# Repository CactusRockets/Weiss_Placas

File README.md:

# Placa de Iluminação Weiss

Placa de acionamento de iluminação desenvolvida em **KiCad**, responsável por controlar dois LEDs com o objetivo de iluminar a parte interna do weiss através de uma chave (push-button), a partir de uma alimentação externa de **3.3V**. O projeto foi desenhado para ser simples e robusto, priorizando facilidade de montagem (todos os componentes em THT) e baixo custo.

## Visão geral do circuito

O circuito é alimentado externamente via um conector **JST XH de 2 vias**, que entrega +3.3V e GND à placa. Essa alimentação passa por um **push-button (SW1)**, que atua como chave liga/desliga geral do circuito. A partir do botão, a alimentação se divide em **dois ramos em paralelo**, cada um composto por um resistor limitador de corrente em série com um LED de alta potência:

Ou seja: quando o botão é pressionado (ou travado, dependendo do tipo de chave utilizada), o circuito fecha e os dois LEDs acendem simultaneamente. Cada LED possui seu próprio resistor, de forma que o brilho e a corrente de cada um são definidos de forma independente — isso evita que uma eventual diferença entre os dois LEDs (tensão direta, tolerância) afete o outro ramo, como aconteceria se estivessem em paralelo direto sob um único resistor.

Foram incluídas **PWR_FLAGs** no esquemático em +3.3V e GND. Elas não fazem parte do circuito fisicamente: servem apenas para informar ao ERC (Electrical Rules Checker) do KiCad que esses nós de alimentação são supridos por uma fonte externa (o JST), evitando falsos positivos de "net não alimentada".

## Componentes

| Referência | Componente | Footprint / Símbolo | Função |
|---|---|---|---|
| **JST1** | Conector JST XH 2 vias | `Connector_JST:JST_XH_B2B-XH-A_1x02_P2.50mm_Vertical` | Entrada de alimentação externa (+3.3V e GND) |
| **SW1** | Push-button | `Button_Switch_SMD:SW_SPST_B3S-1000` (footprint na placa: `SW_SPST_Omron_B3F-40xx-CRD`) | Chave de acionamento (liga/desliga) do circuito |
| **R1** | Resistor 15Ω | `Resistor_THT:R_Axial_DIN0204_L3.6mm_D1.6mm_P7.62mm_Horizontal` | Limitador de corrente do LED U1 |
| **R2** | Resistor 15Ω | `Resistor_THT:R_Axial_DIN0204_L3.6mm_D1.6mm_P7.62mm_Horizontal` | Limitador de corrente do LED U2 |
| **U1** | LED de alta potência | `LED_THT:LED_D5.0mm` | Iluminação (ramo 1) |
| **U2** | LED de alta potência | `LED_THT:LED_D5.0mm` | Iluminação (ramo 2) |

> Os símbolos `JST_basic`, `Push_button_4_pin` e `Led_High` são customizados e estão definidos na biblioteca local `CRD_KICAD.kicad_sym`, criada para padronizar os componentes usados nos projetos da Cactus Rockets.

## Funcionamento

O funcionamento da placa é puramente analógico/passivo — não há microcontrolador ou lógica embarcada:

1. A alimentação de +3.3V chega pelo conector **JST1**.
2. O **SW1** atua como interruptor: enquanto estiver fechado, a corrente flui para os dois ramos de LED.
3. Cada ramo (R + LED) limita a corrente que passa pelo respectivo LED, garantindo que ele opere dentro da faixa segura especificada pelo fabricante, evitando queima por excesso de corrente.
4. O retorno de ambos os ramos é feito para o **GND** comum da placa, que fecha o circuito de volta à fonte externa.

Por não haver controle ativo (PWM, microcontrolador, etc.), o brilho dos LEDs é fixo e definido unicamente pelo valor dos resistores e pela tensão de alimentação — não há dimerização nem controle remoto nesta versão da placa.

## Cálculo dos resistores limitadores

O valor do resistor limitador é definido pela equação pela lei de ohm:

```
R = (V_fonte - V_LED) / I_LED
```

Com `V_fonte = 3.3V` e `R = 15Ω`, a corrente em cada ramo depende da tensão direta (V_f) do LED utilizado. Por exemplo:

- Para um LED com V_f ≈ 2.0V → I ≈ (3.3 − 2.0) / 15 ≈ **87 mA**
- Para um LED com V_f ≈ 3.0V → I ≈ (3.3 − 3.0) / 15 ≈ **20 mA**

## Placa (PCB)

- Placa de **1.6mm** de espessura (FR4 padrão), com contorno definido em `Edge.Cuts`.
- Todos os componentes são **THT** (through-hole), facilitando a montagem manual e a soldagem.
- Footprints utilizados:
  - `CRD_Footprints:SW_SPST_Omron_B3F-40xx-CRD` (SW1)
  - `LED_THT:LED_D5.0mm` / `CRD_Footprints:LED_D5.0mm-CRD` (U1, U2)
  - `Resistor_THT:R_Axial_DIN0204_L3.6mm_D1.6mm_P7.62mm_Horizontal` (R1, R2)
  - `Connector_JST:JST_XH_B2B-XH-A_1x02_P2.50mm_Vertical` (JST1)

## Arquivos do projeto

| Arquivo | Descrição |
|---|---|
| `Placa_de_Iluminação_Weiss.kicad_sch` | Esquemático elétrico da placa |
| `Placa_de_Iluminação_Weiss.kicad_pcb` | Layout da placa (PCB) |
| `Placa_de_Iluminação_Weiss.kicad_pro` | Arquivo de projeto do KiCad |
| `CRD_KICAD.kicad_sym` | Biblioteca de símbolos customizados da Cactus Rockets |
| `fp-lib-table` | Tabela de bibliotecas de footprints usadas no projeto |

# Placa de Processamento — Weiss

Placa eletrônica central do projeto **Weiss**, desenvolvida em **KiCad**, responsável por concentrar o processamento, a aquisição de dados, o armazenamento local e as interfaces de telemetria e sinalização do sistema.

O projeto utiliza um **ESP32 DevKit V1** como controlador principal e integra módulos de rádio LoRa, GPS, cartão microSD, barômetro, unidade inercial, buzzer, LED de status e conectores para sinais externos.

> **Atenção:** esta documentação foi levantada a partir do esquemático e do layout da placa. Antes da fabricação ou da integração ao veículo, execute ERC/DRC no KiCad e confira a pinagem com o firmware e com os módulos físicos utilizados.

## Visão geral

Principais recursos:

- ESP32 DevKit V1 como unidade de processamento;
- telemetria por módulo LoRa **E22-400T30D**;
- posicionamento por módulo GPS serial;
- registro de dados em cartão microSD via SPI;
- medição de pressão e altitude com **BMP390** via I²C;
- medição inercial com **MPU6050** via I²C;
- buzzer e LED para sinalização local;
- duas entradas provenientes de optoacopladores externos;
- duas linhas de interface identificadas como `SKIB1` e `SKIB2`;
- alimentação por bateria de 9 V, com chave e duas linhas reguladas de 5 V;
- conectores JST de 2 vias para alimentação e sinais auxiliares.

## Arquitetura elétrica

```mermaid
flowchart LR
    B["Bateria 9 V"] --> S["Chave SS-5GL"]
    S --> VIN["VIN"]
    VIN --> R1["Regulador 5 V — VOUT"]
    VIN --> R2["Regulador 5 V — VOUT_LORA"]
    R1 --> ESP["ESP32 DevKit V1"]
    R2 --> LORA["LoRa E22-400T30D"]
    ESP --> V33["Barramento 3,3 V"]
    V33 --> GPS["GPS"]
    V33 --> I2C["BMP390 + MPU6050"]
    V33 --> SD["microSD"]
    ESP <--> LORA
    ESP <--> GPS
    ESP <--> I2C
    ESP <--> SD
```

A chave `U$12` conecta o terminal comum `VIN` ao contato associado a `V_BATTERY`; o outro contato da chave aparece sem conexão no esquemático. A partir de `VIN`, dois reguladores independentes, ambos identificados como **5 V**, geram:

- `VOUT`: alimentação do pino `VIN` do ESP32 DevKit V1;
- `VOUT_LORA`: alimentação dedicada do módulo LoRa.

O barramento de **3,3 V** é distribuído a partir do pino `3V3` do ESP32 para os sensores, GPS, microSD e conectores auxiliares. Todos os subsistemas da placa compartilham o mesmo GND.

## Mapeamento de pinos do ESP32

| GPIO | Rede | Interface / função |
|---:|---|---|
| 2 | `LED1` | LED de status |
| 4 | `TX1` | TX do ESP32 para RX do GPS |
| 5 | `CS` | Chip Select do microSD |
| 12 | `SKIB2` | Linha externa SKIB2 |
| 13 | `SKIB1` | Linha externa SKIB1 |
| 14 | `BUZZER` | Acionamento do buzzer |
| 15 | `RX1` | RX do ESP32 vindo do TX do GPS |
| 16 | `RX2` | RX do ESP32 vindo do TXD do LoRa |
| 17 | `TX2` | TX do ESP32 para RXD do LoRa |
| 18 | `CLK` | Clock SPI do microSD |
| 19 | `MISO` | Dados SPI do microSD para o ESP32 |
| 21 | `SDA` | Dados do barramento I²C |
| 22 | `SCL` | Clock do barramento I²C |
| 23 | `MOSI` | Dados SPI do ESP32 para o microSD |
| 32 | `M1` | Seleção de modo do LoRa |
| 33 | `M0` | Seleção de modo do LoRa |
| 34 | `OPTOACOPLADOR2` | Entrada externa isolada |
| 35 | `OPTOACOPLADOR1` | Entrada externa isolada |

> Os GPIOs 34 e 35 do ESP32 são somente de entrada. As linhas `SKIB1` e `SKIB2` chegam diretamente ao ESP32 no esquema apresentado; elas são sinais lógicos e **não devem acionar cargas pirotécnicas diretamente**. Qualquer carga desse tipo exige estágio externo de potência, intertravamentos e isolamento apropriados.

## Interfaces dos módulos

### LoRa E22-400T30D

| Pino do módulo | Rede da placa | Destino |
|---|---|---|
| `VCC` | `VOUT_LORA` | Alimentação dedicada de 5 V |
| `GND` | `GND` | Referência comum |
| `TXD` | `RX2` | GPIO16 do ESP32 |
| `RXD` | `TX2` | GPIO17 do ESP32 |
| `M0` | `M0` | GPIO33 do ESP32 |
| `M1` | `M1` | GPIO32 do ESP32 |
| `AUX` | Sem conexão | Reservado no layout atual |

### GPS

| Pino do módulo | Rede da placa | Destino |
|---|---|---|
| `VCC` | `3V3` | Alimentação de 3,3 V |
| `GND` | `GND` | Referência comum |
| `RX` | `TX1` | GPIO4 do ESP32 |
| `TX` | `RX1` | GPIO15 do ESP32 |

### BMP390 e MPU6050

Os dois sensores compartilham o barramento I²C:

| Sinal | GPIO do ESP32 | Módulos |
|---|---:|---|
| `SDA` | 21 | BMP390 e MPU6050 |
| `SCL` | 22 | BMP390 e MPU6050 |
| `3V3` | — | Alimentação |
| `GND` | — | Referência comum |

No layout atual, os pinos auxiliares `CS`, `SDO` e `INT` do BMP390 e `XDA`, `XCL`, `ADO` e `INT` do MPU6050 não são utilizados.

### Cartão microSD

| Sinal | GPIO do ESP32 |
|---|---:|
| `CS` | 5 |
| `CLK` | 18 |
| `MISO` | 19 |
| `MOSI` | 23 |
| `VCC` | 3,3 V |
| `GND` | GND |

## Conectores auxiliares

| Referência | Identificação | Pino 1 | Pino 2 |
|---|---|---|---|
| `U$10` | Bateria 9 V | `V_BATTERY` | `GND` |
| `U$6` | Skibs | `SKIB1` | `SKIB2` |
| `U$7` | Optoacopladores | `OPTOACOPLADOR1` | `OPTOACOPLADOR2` |
| `U$4` | Buzzer / 3,3 V | `BUZZER` | `3V3` |
| `U$5` | GND / 3,3 V | `3V3` | `GND` |

## Componentes principais

| Referência | Componente | Função |
|---|---|---|
| `U$11` | ESP32 DevKit V1 | Processamento e controle das interfaces |
| `U$2` | E22-400T30D | Comunicação LoRa |
| `U$3` | GPS Module | Posicionamento e referência de tempo |
| `U$1` | BMP390 | Pressão atmosférica e altitude |
| `U$9` | MPU6050 | Acelerômetro e giroscópio |
| `U$8` | MicroSD Small Reader | Armazenamento local de dados |
| `IC1` | Regulador 5 V | Alimentação `VOUT` do ESP32 |
| `IC2` | Regulador 5 V | Alimentação `VOUT_LORA` |
| `U$12` | Chave SS-5GL | Comutação da alimentação de entrada |
| `SP1` | AL60P | Buzzer |
| `LED1` | LED vermelho 5 mm | Indicação visual |
| `R1` | 220 Ω | Limitação de corrente do LED |
| `R2` | 46 Ω | Componente auxiliar; o pad 2 está sem conexão funcional no layout atual |
| `U$4` a `U$7`, `U$10` | JST 2,54 mm, 2 vias | Alimentação e sinais externos |

## Dimensões e construção da PCB

- dimensões aproximadas do contorno: **150 × 80 mm**;
- espessura configurada: **1,6 mm**;
- placa de duas camadas de cobre (`F.Cu` e `B.Cu`);
- componentes predominantemente THT e módulos montados por barras de pinos;
- planos de cobre e trilhas de alimentação de maior largura;
- footprints personalizados disponíveis na biblioteca local `Weiss.pretty`.

## Arquivos do projeto

| Caminho | Descrição |
|---|---|
| `Esquema.kicad_pro` | Projeto principal do KiCad |
| `Esquema.kicad_sch` | Esquemático elétrico |
| `Esquema.kicad_pcb` | Layout da PCB |
| `Esquema.svg` | Exportação vetorial do esquemático |
| `Esquema.kicad_dru` | Regras personalizadas da placa |
| `Weiss.pretty/` | Biblioteca local de footprints |
| `BibliotecasCRD-KiCad-main/` | Bibliotecas auxiliares utilizadas pelo projeto |
| `fp-lib-table` | Tabela de bibliotecas de footprints |
| `sym-lib-table` | Tabela de bibliotecas de símbolos |

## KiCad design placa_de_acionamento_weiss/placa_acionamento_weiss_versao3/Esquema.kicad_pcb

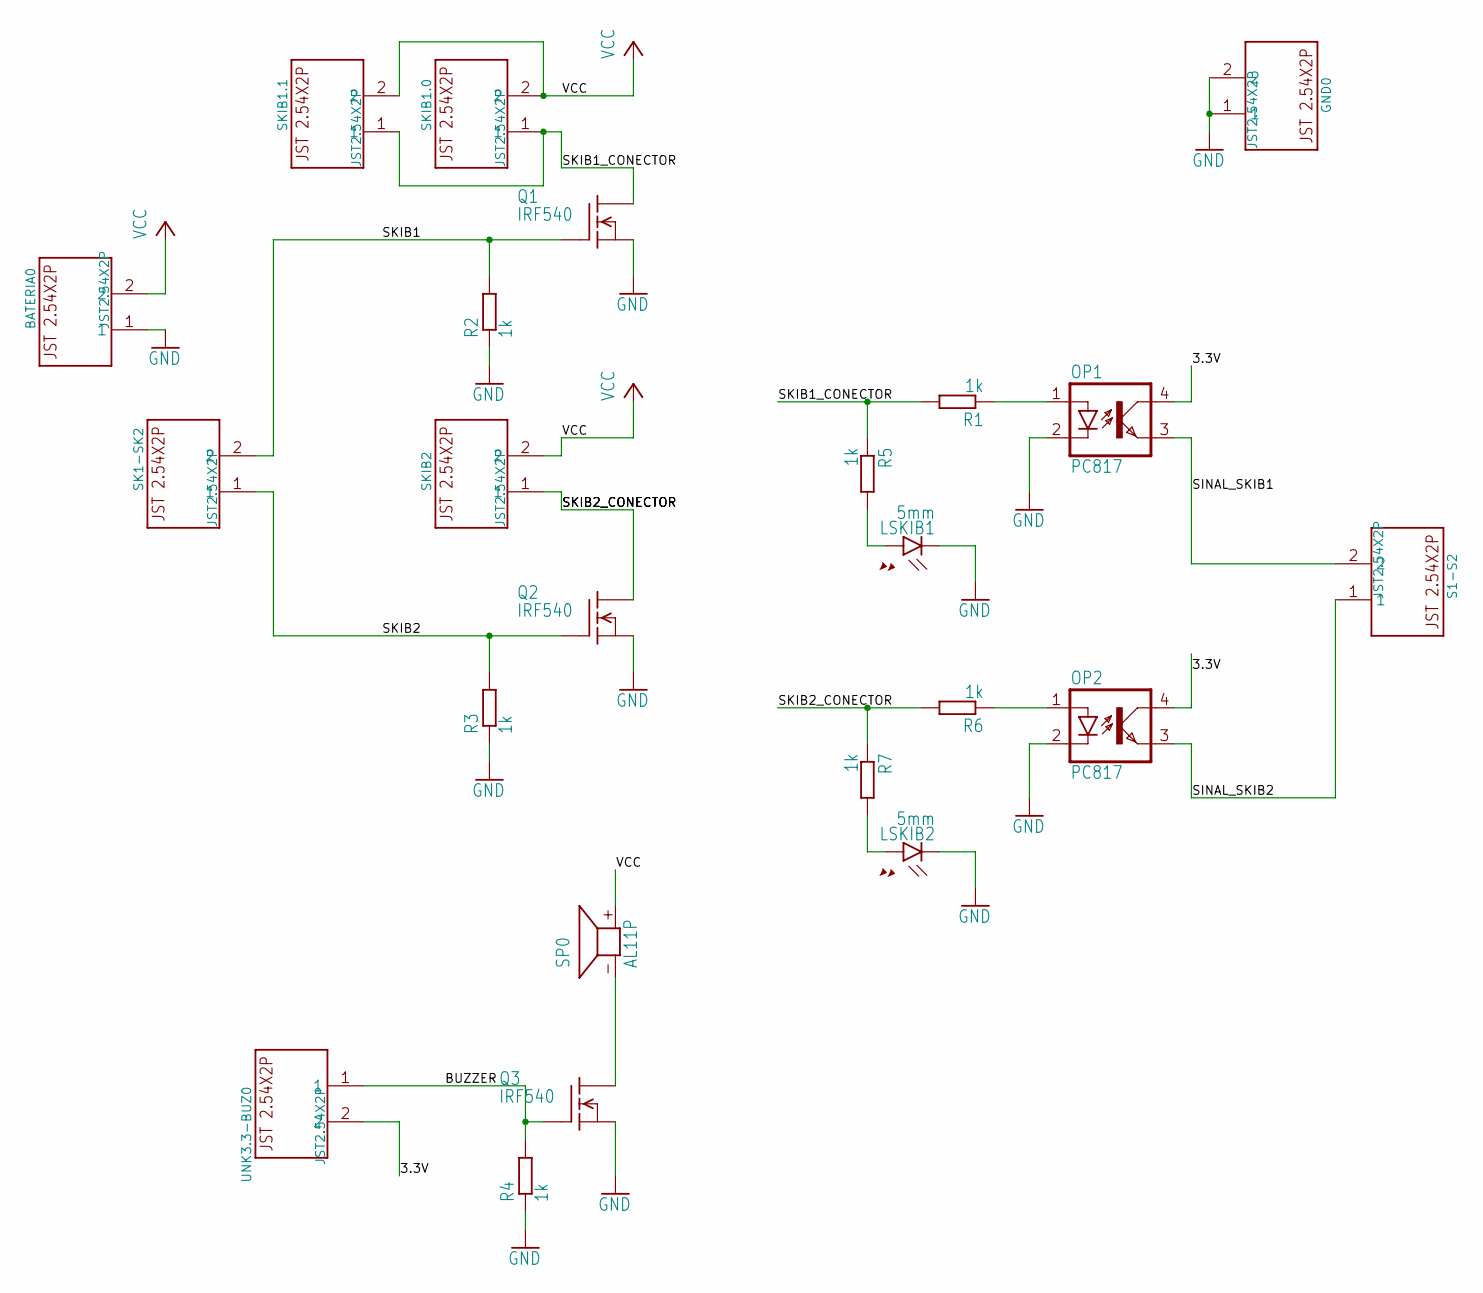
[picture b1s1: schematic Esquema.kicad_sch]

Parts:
BATERIA0: JST2.54X2P; JST2.54X2P_FOOTPRINT
GND0: JST2.54X2P; JST2.54X2P_FOOTPRINT
LSKIB1, LSKIB2: 5mm; LED5MM
OP1, OP2: PC817; DIL04
Q1, Q2, Q3: IRF540; TO220
R1, R2, R3, R4, R5, R6, R7: 1k; 0207_10
S1-S2: JST2.54X2P; JST2.54X2P_FOOTPRINT
SK1-SK2: JST2.54X2P; JST2.54X2P_FOOTPRINT
SKIB1.0, SKIB1.1, SKIB2: JST2.54X2P; JST2.54X2P_FOOTPRINT
SP0: AL11P
UNK3.3-BUZ0: JST2.54X2P; JST2.54X2P_FOOTPRINT

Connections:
3.3V: OP1.4 (COL), OP2.4 (COL), UNK3.3-BUZ0.2
BUZZER: Q3.1 (G), R4.2, UNK3.3-BUZ0.1
GND: BATERIA0.1, GND0.1, GND0.2, LSKIB1.K (C), LSKIB2.K (C), OP1.2 (C), OP2.2 (C), Q1.3 (S), Q2.3 (S), Q3.3 (S), R2.1, R3.1, R4.1
unnamed: LSKIB2.A, R7.2
unnamed: Q3.2 (D), SP0.- (1)
unnamed: LSKIB1.A, R5.2
unnamed: OP1.1 (A), R1.1
unnamed: OP2.1 (A), R6.1
SINAL_SKIB1: OP1.3 (EMIT), S1-S2.2
SINAL_SKIB2: OP2.3 (EMIT), S1-S2.1
SKIB1: Q1.1 (G), R2.2, SK1-SK2.2
SKIB1_CONECTOR: Q1.2 (D), R1.2, R5.1, SKIB1.0.1, SKIB1.1.1
SKIB2: Q2.1 (G), R3.2, SK1-SK2.1
SKIB2_CONECTOR: Q2.2 (D), R6.2, R7.1, SKIB2.1
VCC: BATERIA0.2, SKIB1.0.2, SKIB1.1.2, SKIB2.2, SP0.+ (2)

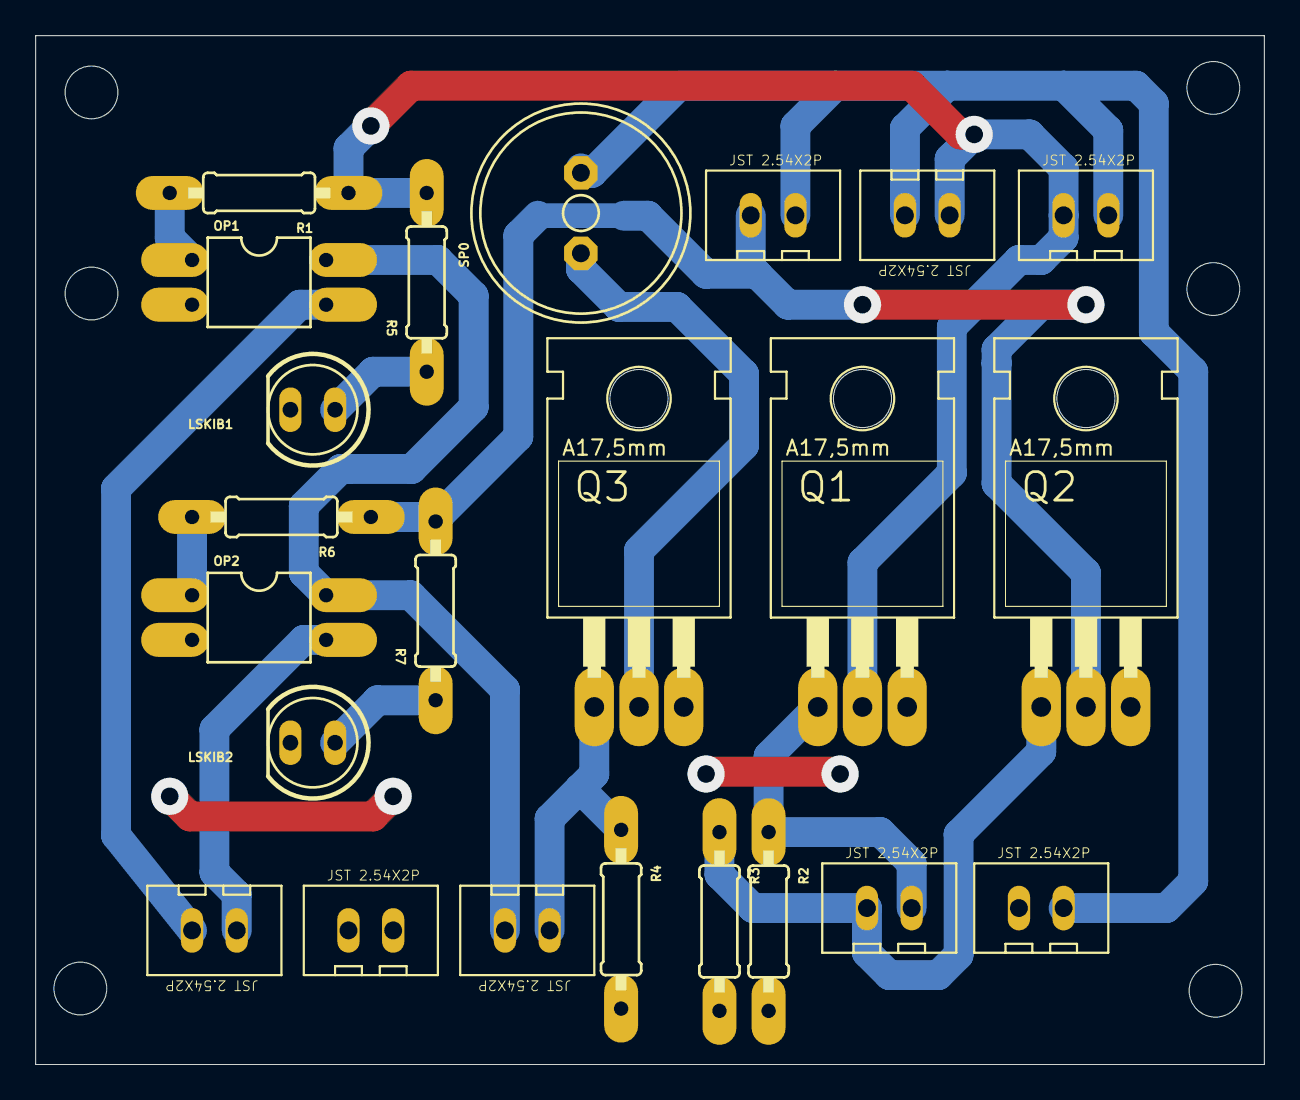
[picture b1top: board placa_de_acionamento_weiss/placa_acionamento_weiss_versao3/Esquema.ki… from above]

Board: 2 copper layers, 69.8 x 58.5 mm, 29 parts (0 on the bottom side), 15 nets.

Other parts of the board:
UNK_HOLE_0: dummyfp0
UNK_HOLE_1: dummyfp1
UNK_HOLE_2: dummyfp2
UNK_HOLE_3: dummyfp3
UNK_HOLE_4: dummyfp4
UNK_HOLE_5: dummyfp5

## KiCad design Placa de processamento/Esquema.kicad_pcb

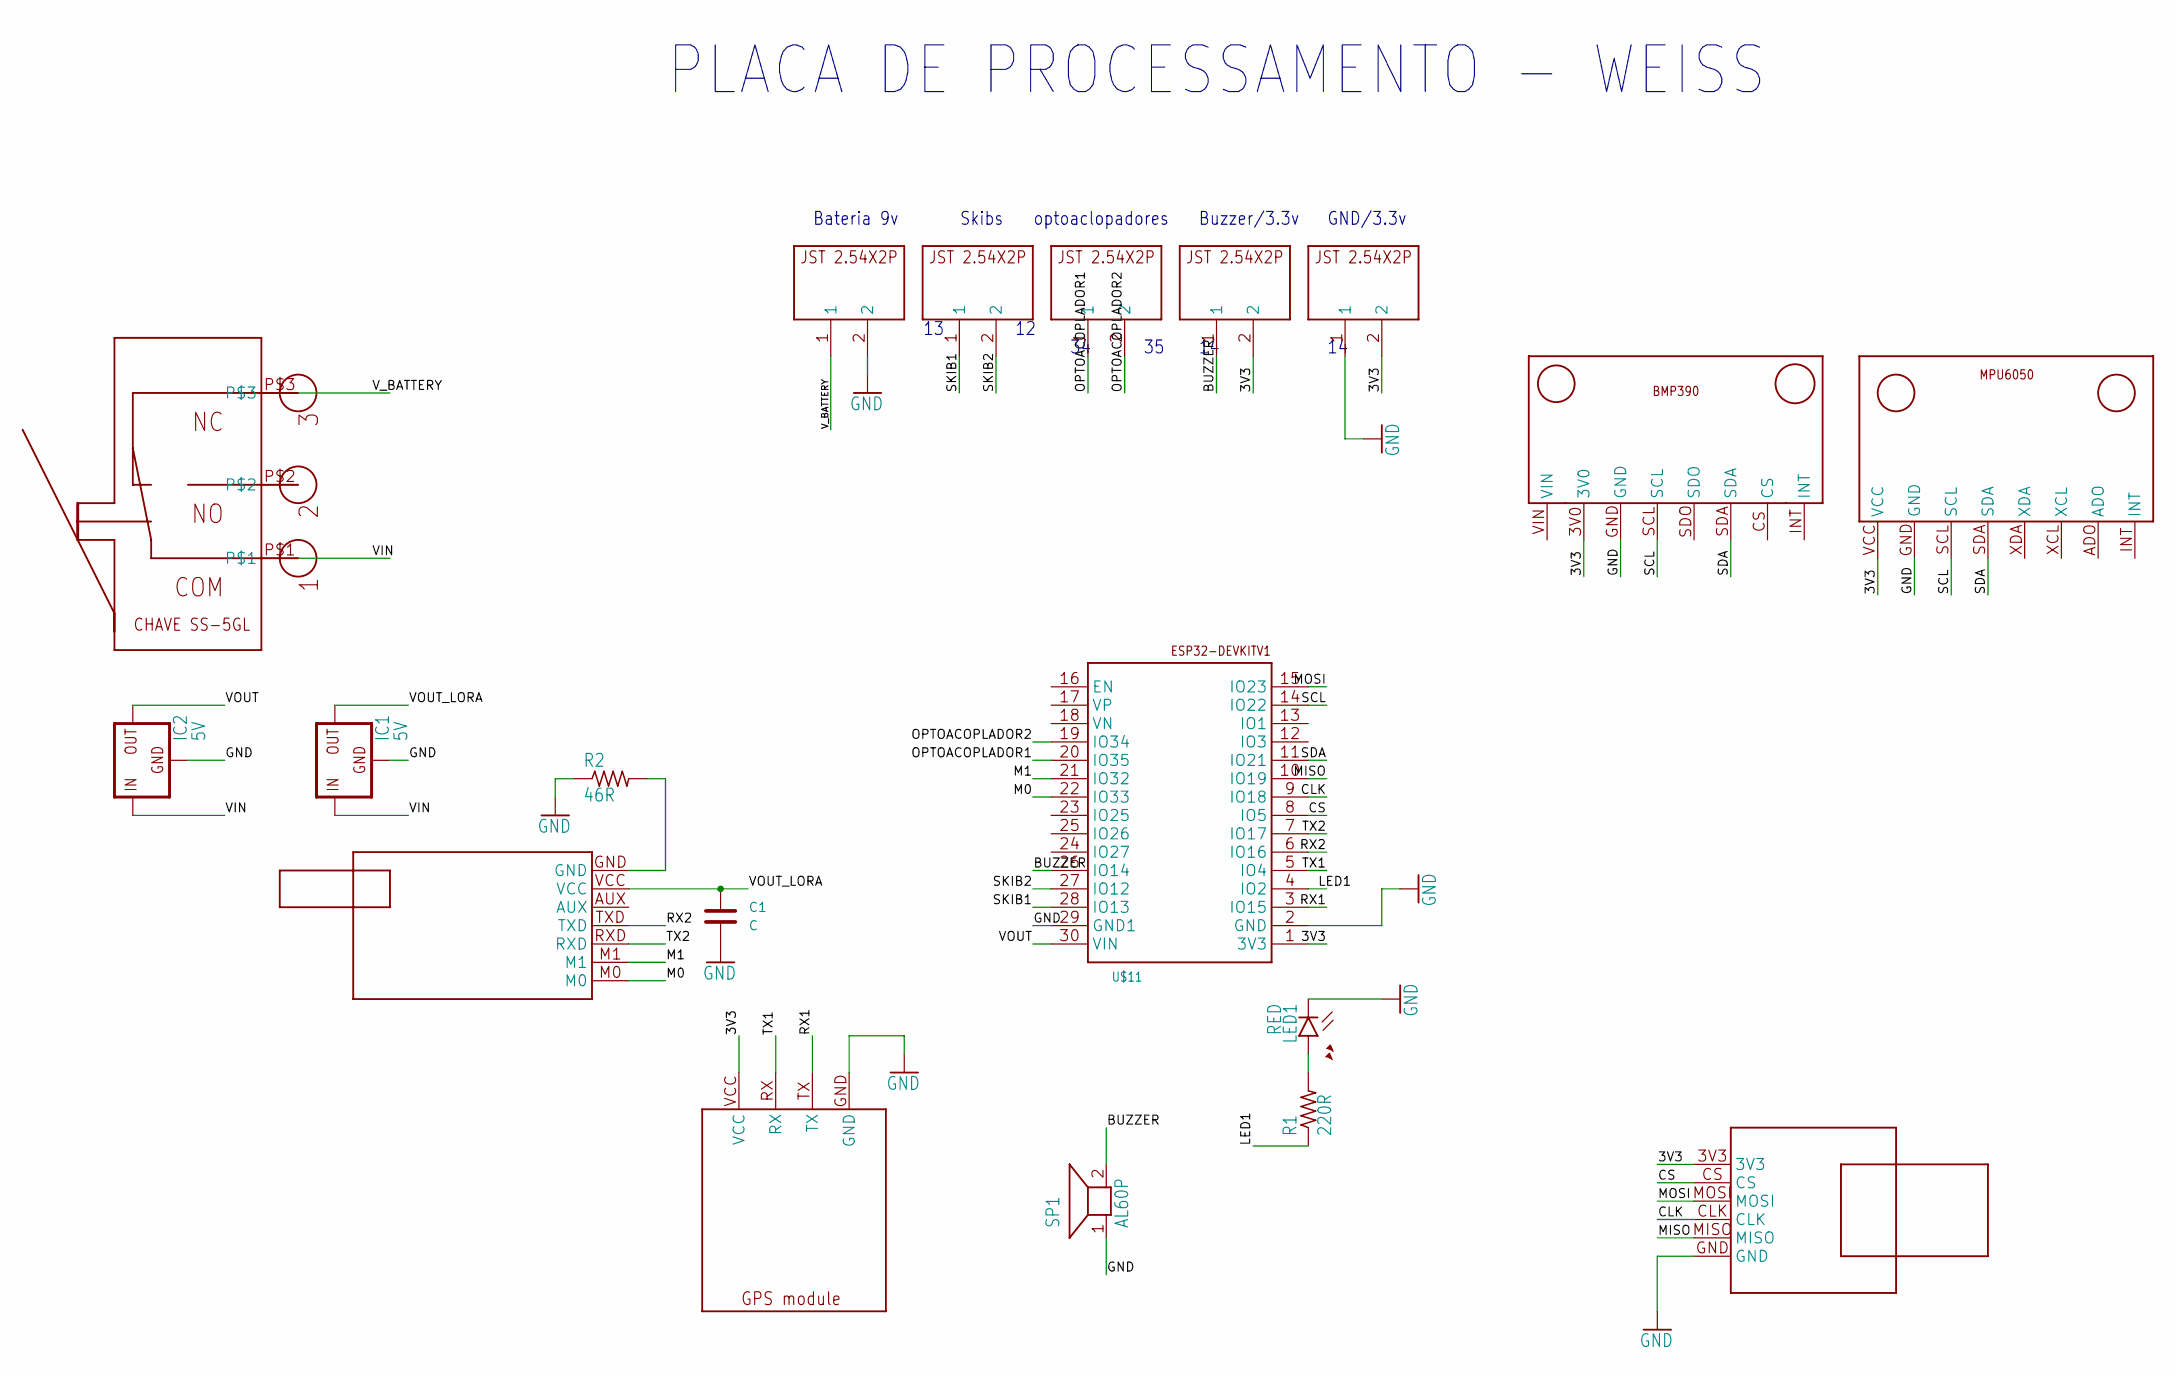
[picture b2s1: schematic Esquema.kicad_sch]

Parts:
C1: C
IC1, IC2: 5V; 78XXL
LED1: RED; LED5MM
R1: 220R; 0309_12
R2: 46R; 0309_12
SP1: AL60P
U$1: BMP390V1; BMP390_FOOTPRINT
U$2: E22-400T30D; E22-400T30D_FOOTPRINT
U$3: GPS_MODULE; GPS_MODULE_FOOTPRINT
U$4, U$5, U$6, U$7: JST2.54X2P; JST2.54X2P_FOOTPRINT
U$8: MICROSD_SMALL_READER; MICROSD_SMALL_READER_FOOTPRINT
U$9: MPU6050V1; MPU6050_FOOTPRINT
U$10: JST2.54X2P; JST2.54X2P_FOOTPRINT_39051337
U$11: ESP32DEVKITV1; ESP32-DEVKITV1
U$12: CHAVE_SS-5GL; CHAVESS-5GL

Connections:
/3V3: U$1.3V0, U$3.VCC, U$4.2, U$8.3V3, U$9.VCC, U$10.2, U$11.1 (3V3)
/BUZZER: SP1.2, U$4.1, U$11.26 (IO14)
/CLK: U$8.CLK, U$11.9 (IO18)
/CS: U$8.CS, U$11.8 (IO5)
/LED1: R1.1, U$11.4 (IO2)
/M0: U$2.M0, U$11.22 (IO33)
/M1: U$2.M1, U$11.21 (IO32)
/MISO: U$8.MISO, U$11.10 (IO19)
/MOSI: U$8.MOSI, U$11.15 (IO23)
/OPTOACOPLADOR1: U$5.1, U$11.20 (IO35)
/OPTOACOPLADOR2: U$5.2, U$11.19 (IO34)
/RX1: U$3.TX, U$11.3 (IO15)
/RX2: U$2.TXD, U$11.6 (IO16)
/SCL: U$1.SCL, U$9.SCL, U$11.14 (IO22)
/SDA: U$1.SDA, U$9.SDA, U$11.11 (IO21)
/SKIB1: U$6.1, U$11.28 (IO13)
/SKIB2: U$6.2, U$11.27 (IO12)
/TX1: U$3.RX, U$11.5 (IO4)
/TX2: U$2.RXD, U$11.7 (IO17)
/VIN: IC1.IN, IC2.IN, U$12.P$1
/VOUT: IC2.OUT, U$11.30 (VIN)
/VOUT_LORA: C1.1, IC1.OUT, U$2.VCC
/V_BATTERY: U$7.1, U$12.P$3
GND: C1.2, IC1.GND, IC2.GND, LED1.K (C), R2.1, SP1.1, U$1.GND, U$3.GND, U$7.2, U$8.GND, U$9.GND, U$10.1, U$11.2 (GND), U$11.29 (GND1)
unnamed: LED1.A, R1.2
unnamed: R2.2, U$2.GND

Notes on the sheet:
Bateria 9v
PLACA DE PROCESSAMENTO - WEISS
Skibs
GND/3.3v
Buzzer/3.3v
optoaclopadores

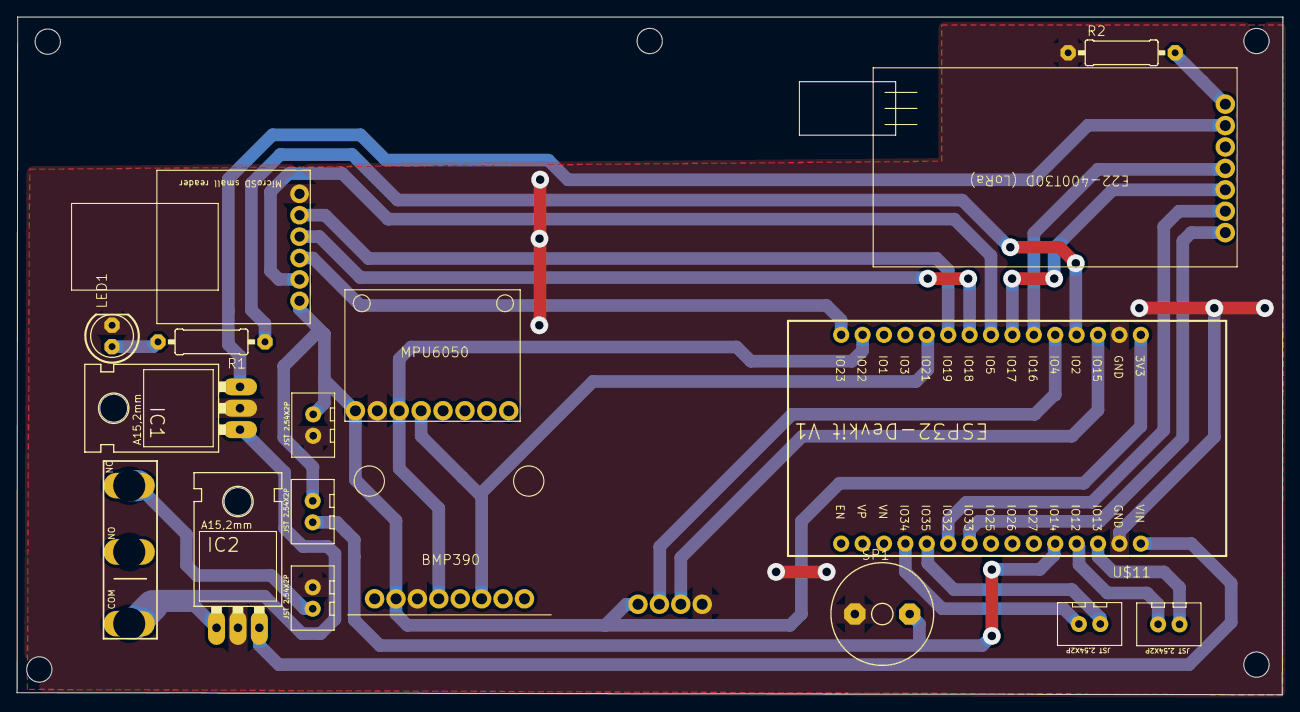
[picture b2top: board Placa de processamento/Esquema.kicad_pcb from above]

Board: 2 copper layers, 150.2 x 80.4 mm, 23 parts (1 on the bottom side), 26 nets.

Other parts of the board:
UNK_HOLE_0: dummyfp0
UNK_HOLE_1: dummyfp1
UNK_HOLE_2: dummyfp2
UNK_HOLE_3: dummyfp3
UNK_HOLE_4: dummyfp4

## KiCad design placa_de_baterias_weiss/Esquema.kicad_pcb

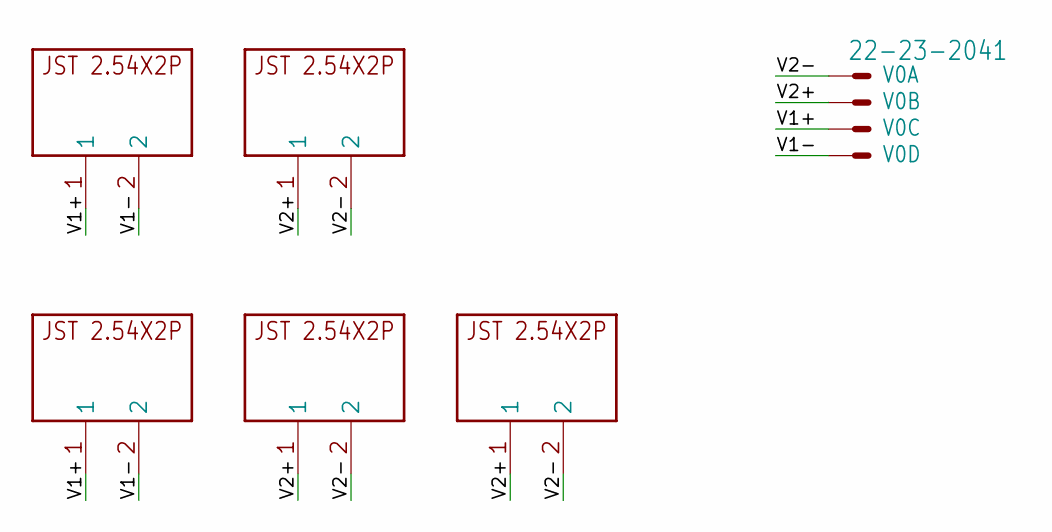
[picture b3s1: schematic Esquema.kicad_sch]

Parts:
U$1, U$2, U$3, U$4, U$5: JST2.54X2P; JST2.54X2P_FOOTPRINT
V0: 22-23-2041

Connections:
V1+: U$1.1, U$4.1, V0.3
V1-: U$1.2, U$4.2, V0.4
V2+: U$2.1, U$3.1, U$5.1, V0.2
V2-: U$2.2, U$3.2, U$5.2, V0.1

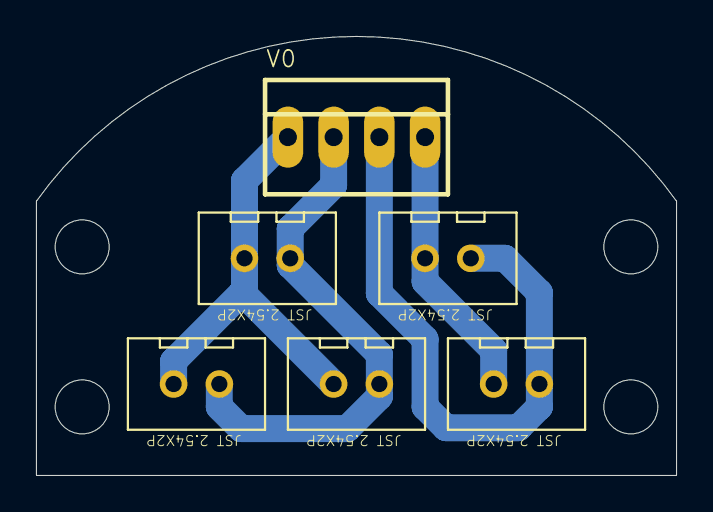
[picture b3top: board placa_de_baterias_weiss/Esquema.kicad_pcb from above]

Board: 2 copper layers, 35.6 x 24.4 mm, 10 parts (0 on the bottom side), 4 nets.

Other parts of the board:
UNK_HOLE_0: dummyfp0
UNK_HOLE_1: dummyfp1
UNK_HOLE_2: dummyfp2
UNK_HOLE_3: dummyfp3

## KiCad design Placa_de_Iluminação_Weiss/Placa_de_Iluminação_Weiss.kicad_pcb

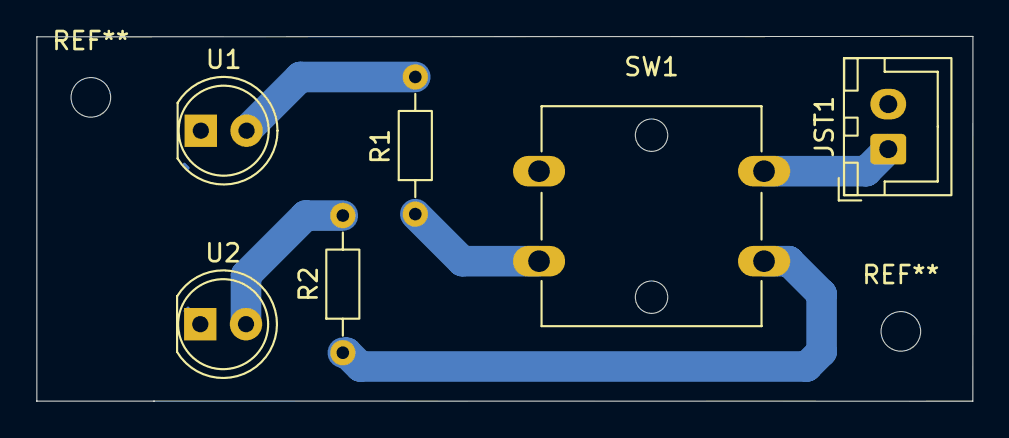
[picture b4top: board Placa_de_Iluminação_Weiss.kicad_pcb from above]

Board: 2 copper layers, 52.0 x 20.3 mm, 6 parts (0 on the bottom side), 6 nets.

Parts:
JST1: JST_XH_B2B-XH-A_1x02_P2.50mm_Vertical
R1, R2: 15Ω; R_Axial_DIN0204_L3.6mm_D1.6mm_P7.62mm_Horizontal
SW1: SW_SPST_Omron_B3F-40xx-CRD
U1, U2: LED_D5.0mm-CRD

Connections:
+3.3V: JST1.1 (3.3v), SW1.4 (A)
GND: JST1.2 (GND), U1.2, U2.2
unnamed: R1.1, SW1.2
unnamed: R1.2, U1.1
unnamed: R2.2, U2.1
unnamed: R2.1, SW1.3 (K)
